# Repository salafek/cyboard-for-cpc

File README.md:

# Cyboard for the Amstrad CPC
Cyboard is a [Symbiface II](https://www.cpcwiki.eu/index.php/SYMBiFACE_II) clone with embedded Ethernet controller for the [Amstrad CPC](https://www.cpcwiki.eu/index.php/CPC) range of computers.</br>
Its Ethernet controller is supported by [SymbOS](http://symbos.de) (download the network daemon [here](https://github.com/salafek/Net4CPC/tree/main/Extra)) and by [KCNet utilities](https://github.com/salafek/KCNet-software-for-Net4CPC) for CP/M.</br>

## Interface main components and functions
- Compact Flash Card mass storage device
- PS/2 compatible USB Mouse controller
- Real Time Clock
- Ethernet controller with embedded TCP/IP stack
- Reset button

Unlike Symbiface II, Cyboard doesn't integrate RAM or ROM expansion for the CPC.

All the integrated devices are fully compatible with the original Symbiface II thus using the same [I/O port addresses](https://www.cpcwiki.eu/index.php/SYMBiFACE_II:I/O_Map_Summary).</br>
The interface uses a full 16-bit address decoding. A dual 4-input AND gate 74HCT21 and a GAL20V8 PLD is used for this purpose. All the GAL's outputs are programmed as combinational outputs.</br>
The interface has a [Mother X4](https://cpcrulez.fr/hardware-interface-mother_x4.htm) compatible connector.</br> 
The CF card works in memory mode so it can be directly addressed as an 8-bit device and has no need for initialization via software.</br>
The mouse controller is a [Microchip PIC16F84A](https://www.microchip.com/en-us/product/PIC16F84A) programmed in assembly and it is clocked by the CPCs 4MHz clock. It supports mice with 5 buttons and scroll wheel.</br>
The RTC module is the famous [DS12887](https://www.analog.com/en/products/ds12887.html#product-overview) which is also used in the original Symbiface II.(variants DS12887A, DS12C887, DS12C887A can also be used)</br>
The network module is based on the [WIZnet's W5100S](https://www.wiznet.io/product-item/w5100s/) embedded ethernet controller and works in indirect parallel bus mode.</br>
In this mode it needs 4 I/O ports:
- #FD20: MR - Common Register MR
- #FD21: IDM_ARH - Upper 8 bits Offset Address Register
- #FD22: IDM_ARL - Lower 8 bits Offset Address Register
- #FD23: IDM_DR - 8 Bits Data Register

A detailed description on how to program the module, with flow diagrams and programming examples, can be found at the WIZnet's official site:</br>
[W5100S TCP Function](https://docs.wiznet.io/Product/iEthernet/W5100S/Application-Note/tcp)</br>
[W5100S UDP Function](https://docs.wiznet.io/Product/iEthernet/W5100S/Application-Note/udp)</br>
[SOCKET-less Command](https://docs.wiznet.io/Product/iEthernet/W5100S/Application-Note/socket-less-command)</br>

[The module](https://www.aliexpress.com/w/wholesale-%22W5100S-Network-Module%22-parallel.html?catId=0&initiative_id=SB_20230206005326&SearchText=%22W5100S%20Network%20Module%22%20parallel&spm=a2g0o.productlist.1000002.0) that's been used in this implementation is one with an integrated 3.3V regulator but also the original WIZnet's [W5100S](https://github.com/Wiznet/Hardware-Files-of-WIZnet/tree/master/05_Network_Module/WIZ810SMJ) and [W6100](https://github.com/Wiznet/Hardware-Files-of-WIZnet/tree/master/05_Network_Module/WIZ610MJ) modules can be used instead, with small changes in the design.</br>

## Build info
The schematic and layout were generated with Autodesk EAGLE 9.6.2 free edition</br>
The GAL20V8B files were generated with Atmel WinCupl 5.30.4</br>
The PIC16F84A files were generated with Microchip MPLAB IDE 8.83</br>

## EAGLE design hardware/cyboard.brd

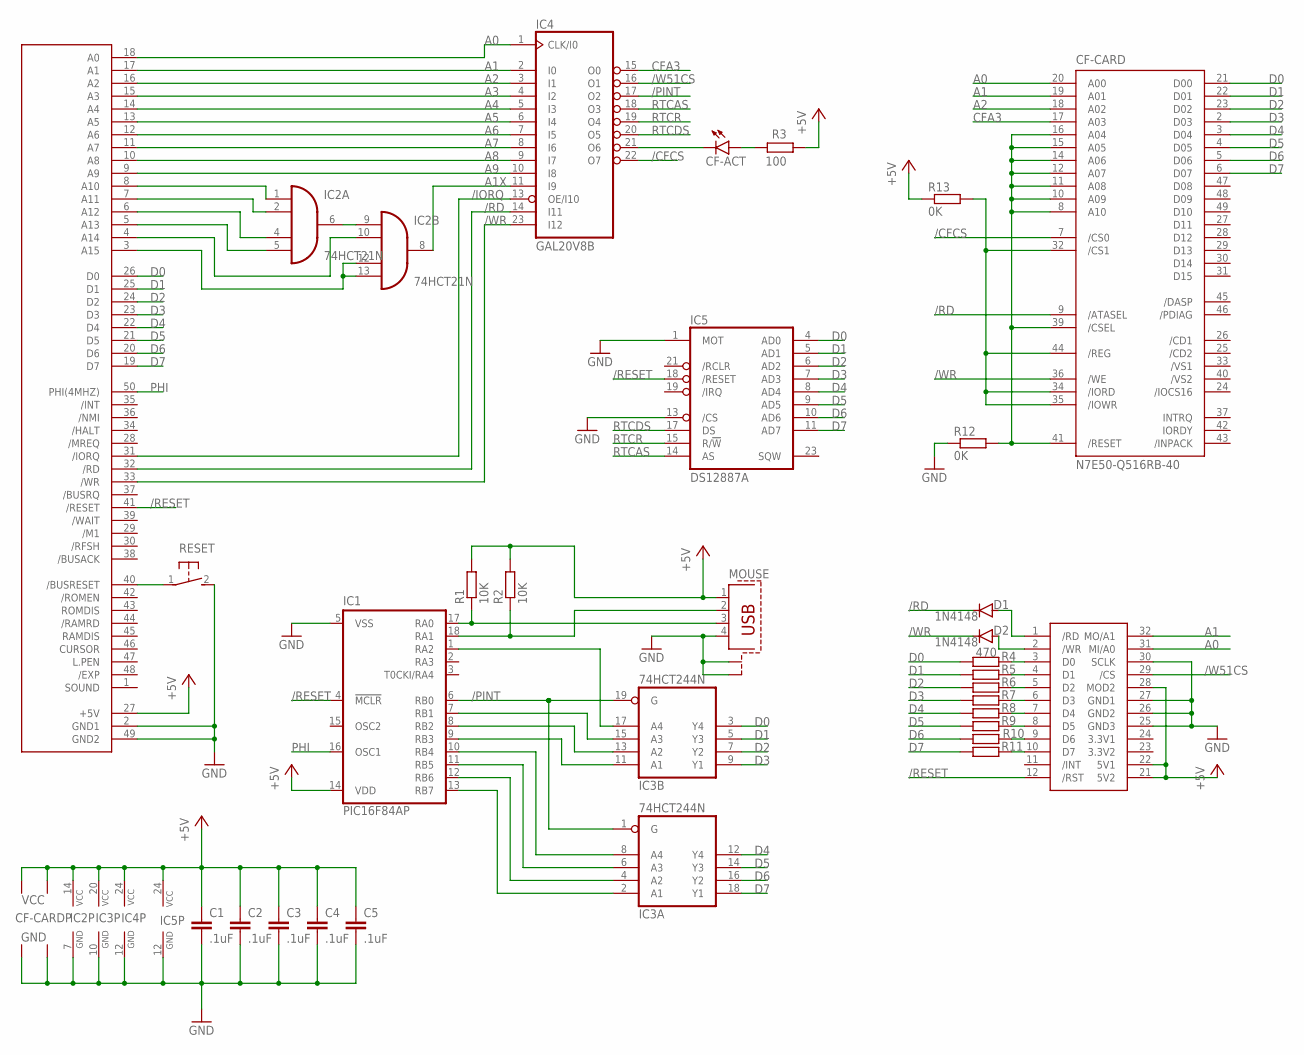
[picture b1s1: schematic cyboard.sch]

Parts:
C1, C2, C3, C4, C5: .1uF; C025-025X050
CF-ACT: CF ACT; LED3MM
CF-CARD: N7E50-Q516RB-40; 3M-N7E50
CON1: CPCBUS; 2X25
D1, D2: 1N4148; DO35-7
IC1: PIC16F84AP; DIL18
IC2: 74HCT21N; DIL14
IC3: 74HCT244N; DIL20
IC4: GAL20V8B; DIL24-3
IC5: DS12887A; DIL24
MOUSE: PN87520-S
R1, R2: 10K; 0204/7
R3: 100; 0204/7
R4, R5, R6, R7, R8, R9, R10, R11: 470; 0204/7
R12, R13: 0K; 0204/7
RESET: Reset; B3F-31XX
W5100S-MODULE: W5100S-NETWORK-MODULE

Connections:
3.3V1: W5100S-MODULE.24 (3.3V1)
3.3V2: W5100S-MODULE.23 (3.3V2)
/BUSRESET: CON1.40 (/BUSRESET), RESET.1
/CFACT: CF-ACT.K (C), IC4.21 (O6)
/CFCS: CF-CARD.7 (/CS0), IC4.22 (O7)
/IORQ: CON1.31 (/IORQ), IC4.13 (OE/I10)
/PINT: IC1.6 (RB0), IC3.1 (G), IC3.19 (G), IC4.17 (O2)
/RD: CF-CARD.9 (/ATASEL), CON1.32 (/RD), D1.C, IC4.14 (I11)
/RESET: CON1.41 (/RESET), IC1.4 (!MCLR), IC5.18 (/RESET), W5100S-MODULE.12 (/RST)
/W51CS: IC4.16 (O1), W5100S-MODULE.29 (/CS)
/W51RD: D1.A, W5100S-MODULE.1 (/RD)
/W51WR: D2.A, W5100S-MODULE.2 (/WR)
/WR: CF-CARD.36 (/WE), CON1.33 (/WR), D2.C, IC4.23 (I12)
A0: CF-CARD.20 (A00), CON1.18 (A0), IC4.1 (CLK/I0), W5100S-MODULE.31 (MI/A0)
A1: CF-CARD.19 (A01), CON1.17 (A1), IC4.2 (I0), W5100S-MODULE.32 (MO/A1)
A1X: IC2.8 (O), IC4.11 (I9)
A2: CF-CARD.18 (A02), CON1.16 (A2), IC4.3 (I1)
A3: CON1.15 (A3), IC4.4 (I2)
A4: CON1.14 (A4), IC4.5 (I3)
A5: CON1.13 (A5), IC4.6 (I4)
A6: CON1.12 (A6), IC4.7 (I5)
A7: CON1.11 (A7), IC4.8 (I6)
A8: CON1.10 (A8), IC4.9 (I7)
A9: CON1.9 (A9), IC4.10 (I8)
A10: CON1.8 (A10), IC2.1 (I0)
A11: CON1.7 (A11), IC2.2 (I1)
A12: CON1.6 (A12), IC2.4 (I2)
A13: CON1.5 (A13), IC2.5 (I3)
A14: CON1.4 (A14), IC2.10 (I1)
A15: CON1.3 (A15), IC2.12 (I2), IC2.13 (I3)
CFA3: CF-CARD.17 (A03), IC4.15 (O0)
CFDN: CF-CARD.8 (A10), CF-CARD.10 (A09), CF-CARD.11 (A08), CF-CARD.12 (A07), CF-CARD.14 (A06), CF-CARD.15 (A05), CF-CARD.16 (A04), CF-CARD.39 (/CSEL), CF-CARD.41 (/RESET), R12.2
CFUP: CF-CARD.32 (/CS1), CF-CARD.34 (/IORD), CF-CARD.35 (/IOWR), CF-CARD.44 (/REG), R13.2
D0: CF-CARD.21 (D00), CON1.26 (D0), IC3.3 (Y4), IC5.4 (AD0), R4.1
D1: CF-CARD.22 (D01), CON1.25 (D1), IC3.5 (Y3), IC5.5 (AD1), R5.1
D2: CF-CARD.23 (D02), CON1.24 (D2), IC3.7 (Y2), IC5.6 (AD2), R6.1
D3: CF-CARD.2 (D03), CON1.23 (D3), IC3.9 (Y1), IC5.7 (AD3), R7.1
D4: CF-CARD.3 (D04), CON1.22 (D4), IC3.12 (Y4), IC5.8 (AD4), R8.1
D5: CF-CARD.4 (D05), CON1.21 (D5), IC3.14 (Y3), IC5.9 (AD5), R9.1
D6: CF-CARD.5 (D06), CON1.20 (D6), IC3.16 (Y2), IC5.10 (AD6), R10.1
D7: CF-CARD.6 (D07), CON1.19 (D7), IC3.18 (Y1), IC5.11 (AD7), R11.1
GND: C1.2, C2.2, C3.2, C4.2, C5.2, CF-CARD.1 (GND1), CF-CARD.50 (GND2), CON1.2 (GND1), CON1.49 (GND2), IC1.5 (VSS), IC2.7 (GND), IC3.10 (GND), IC4.12 (GND), IC5.1 (MOT), IC5.12 (GND), IC5.13 (/CS), MOUSE.4, MOUSE.S1, MOUSE.S2, R12.1, RESET.2 (S), W5100S-MODULE.25 (GND3), W5100S-MODULE.26 (GND2), W5100S-MODULE.27 (GND1), W5100S-MODULE.30 (SCLK)
MOUSED0: IC1.1 (RA2), IC3.17 (A4)
MOUSED1: IC1.7 (RB1), IC3.15 (A3)
MOUSED2: IC1.8 (RB2), IC3.13 (A2)
MOUSED3: IC1.9 (RB3), IC3.11 (A1)
MOUSED4: IC1.10 (RB4), IC3.8 (A4)
MOUSED5: IC1.11 (RB5), IC3.6 (A3)
MOUSED6: IC1.12 (RB6), IC3.4 (A2)
MOUSED7: IC1.13 (RB7), IC3.2 (A1)
unnamed: CF-ACT.A, R3.2
unnamed: IC2.6 (O), IC2.9 (I0)
PHI: CON1.50 (PHI(4MHZ)), IC1.16 (OSC1)
RTCAS: IC4.18 (O3), IC5.14 (AS)
RTCDS: IC4.20 (O5), IC5.17 (DS)
RTCR: IC4.19 (O4), IC5.15 (R/!W)
USBD+: IC1.17 (RA0), MOUSE.3, R1.1
USBD-: IC1.18 (RA1), MOUSE.2, R2.1
VCC: C1.1, C2.1, C3.1, C4.1, C5.1, CF-CARD.13 (VCC2), CF-CARD.38 (VCC1), CON1.27 (+5V), IC1.14 (VDD), IC2.14 (VCC), IC3.20 (VCC), IC4.24 (VCC), IC5.24 (VCC), MOUSE.1, R1.2, R2.2, R3.1, R13.1, W5100S-MODULE.21 (5V2), W5100S-MODULE.22 (5V1), W5100S-MODULE.28 (MOD2)
W51D0: R4.2, W5100S-MODULE.3 (D0)
W51D1: R5.2, W5100S-MODULE.4 (D1)
W51D2: R6.2, W5100S-MODULE.5 (D2)
W51D3: R7.2, W5100S-MODULE.6 (D3)
W51D4: R8.2, W5100S-MODULE.7 (D4)
W51D5: R9.2, W5100S-MODULE.8 (D5)
W51D6: R10.2, W5100S-MODULE.9 (D6)
W51D7: R11.2, W5100S-MODULE.10 (D7)

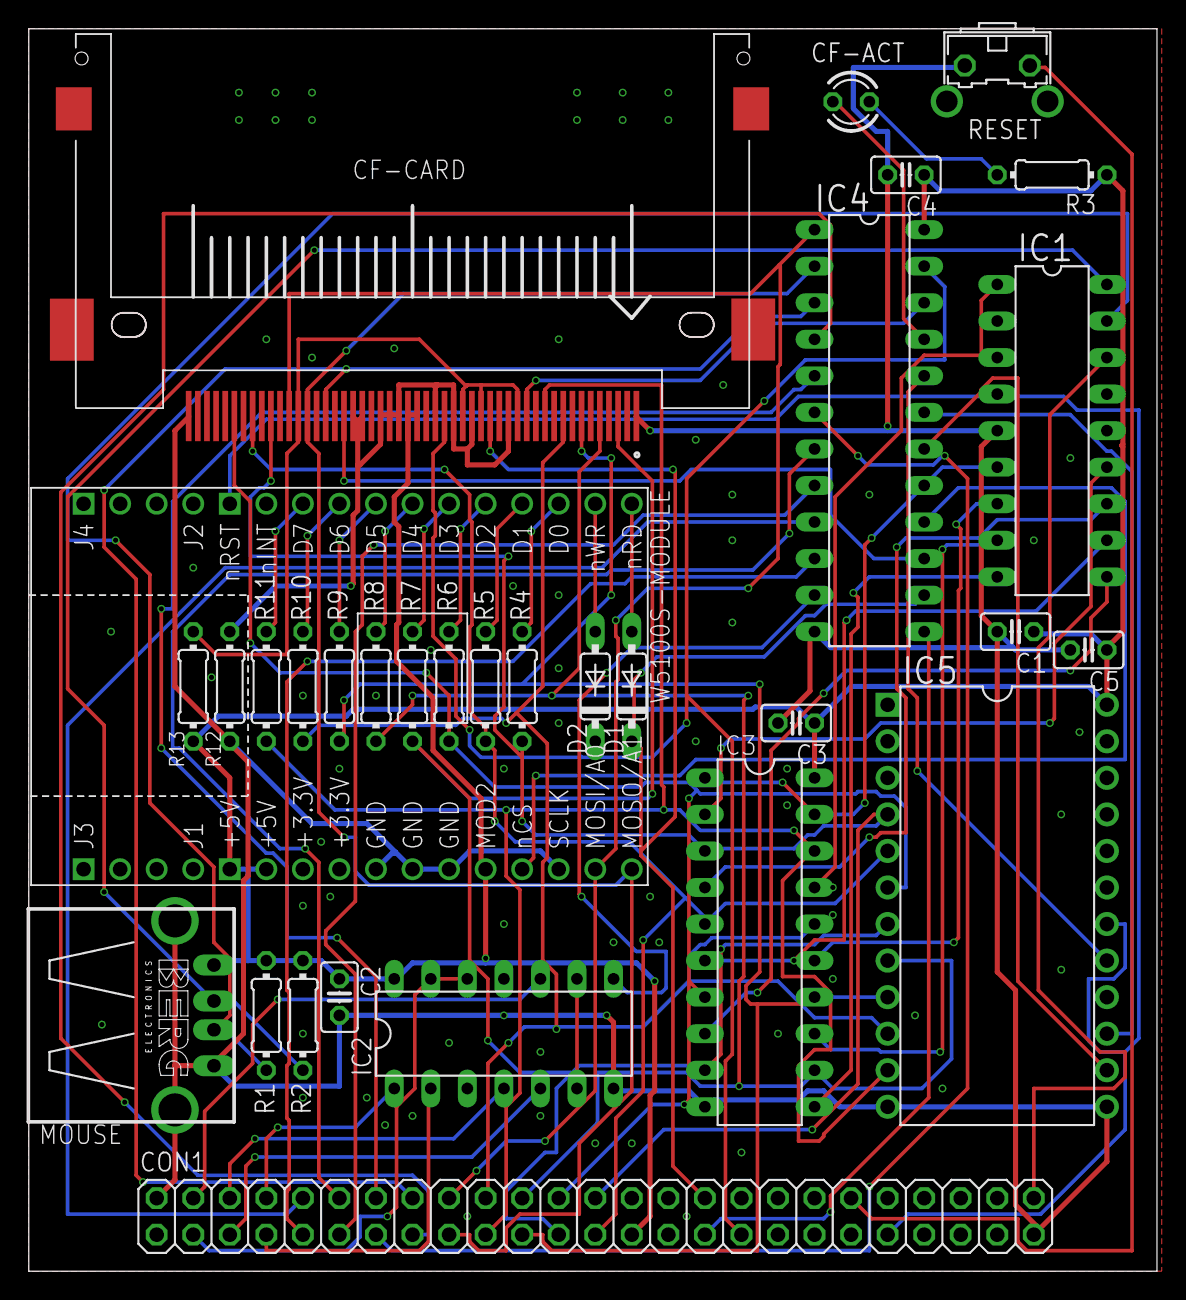
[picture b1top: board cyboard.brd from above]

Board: 2 copper layers, 78.3 x 86.3 mm, 31 parts (0 on the bottom side), 65 nets.

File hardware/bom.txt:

Partlist

Part          Value                 Package               Digi-Key PN

C1            .1uF                  C025/C320             399-9871-1-ND
C2            .1uF                  C025/C320             399-9871-1-ND
C3            .1uF                  C025/C320             399-9871-1-ND
C4            .1uF                  C025/C320             399-9871-1-ND
C5            .1uF                  C025/C320             399-9871-1-ND
CF-ACT        LED WHITE DIFFUSED    LED3MM                1516-QBL7IW60D-CW-ND
CF-CARD       N7E50-Q516RB-40       3M-N7E50              3M5455-ND
CON1          CPCBUS                HEADER R/A 50POS      732-5414-ND
D1            1N4148                DO35-7                2368-1N4148-ND
D2            1N4148                DO35-7                2368-1N4148-ND
IC1           PIC16F84AP            DIL18                 PIC16F84A-04I/P-ND
IC2           74HCT21N              DIL14                 296-9262-5-ND
IC3           74HCT244N             DIL20                 296-1610-5-ND
IC4           GAL20V8B              DIL24-3               2156-GAL20V8Z-15QP-ND
IC5           DS12887A              DIL24                 DS12887+-ND
MOUSE         87520-0012BLF         USB-A RCPT TH R/A     609-87520-0012BLF-ND
R1            10K                   0204/0207             MFR-25FRE52-10K-ND
R2            10K                   0204/0207             MFR-25FRE52-10K-ND
R3            100                   0204/0207             MFR-25FRE52-100R-ND
R4            470                   0204/0207             MFR-25FRF52-470R-ND
R5            470                   0204/0207             MFR-25FRF52-470R-ND
R6            470                   0204/0207             MFR-25FRF52-470R-ND
R7            470                   0204/0207             MFR-25FRF52-470R-ND
R8            470                   0204/0207             MFR-25FRF52-470R-ND
R9            470                   0204/0207             MFR-25FRF52-470R-ND
R10           470                   0204/0207             MFR-25FRF52-470R-ND
R11           470                   0204/0207             MFR-25FRF52-470R-ND
R12           0                     Jumper                
R13           0                     Jumper                
RESET         BF-3120               SWITCH TACT SPST-NO   SW407-ND
W5100S-MODULE W5100S-NETWORK-MODULE W5100S-NETWORK-MODULE

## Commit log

2023-02-05 new file: firmware/gal20v8b/Cyboard.jed new file: firmware/gal20v8b/Cyboard.pld new file: firmware/pic16f84a/ps2_cpc_mouse.asm new file: firmware/pic16f84a/ps2_cpc_mouse.hex new file: hardware/cpc_rc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
2023-02-05 first release renamed: firmware/gal20v8b/Cyboard.jed -> firmware/gal20v8b/cyboard.jed renamed: firmware/gal20v8b/Cyboard.pld -> firmware/gal20v8b/cyboard.pld renamed: hardware/cpc_rct_mouse.brd -> ha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
2023-02-05 Create LICENSE
